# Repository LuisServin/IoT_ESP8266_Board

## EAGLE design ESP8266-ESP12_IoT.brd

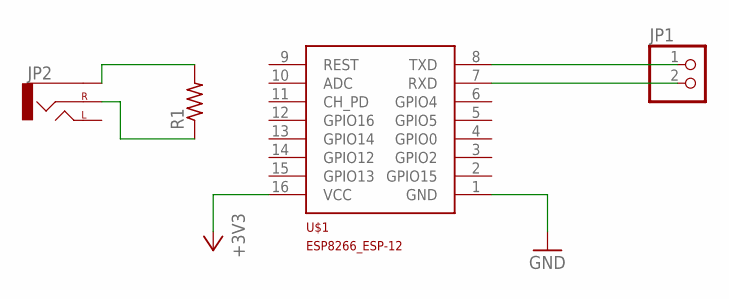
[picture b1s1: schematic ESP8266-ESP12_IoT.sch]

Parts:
JP1: PINHD-1X2/90; 1X02/90
JP2: AUDIO-JACKPTH; AUDIO-JACK
R1: R-US_R0805; R0805
U$1: ESP8266_ESP-12; ESP8266-ESP12

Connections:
+3V3: U$1.16 (VCC)
GND: U$1.1 (GND)
unnamed: JP1.1, U$1.8 (TXD)
unnamed: JP1.2, U$1.7 (RXD)
unnamed: JP2.SLEEVE, R1.2
unnamed: JP2.RING (RIGHT), R1.1

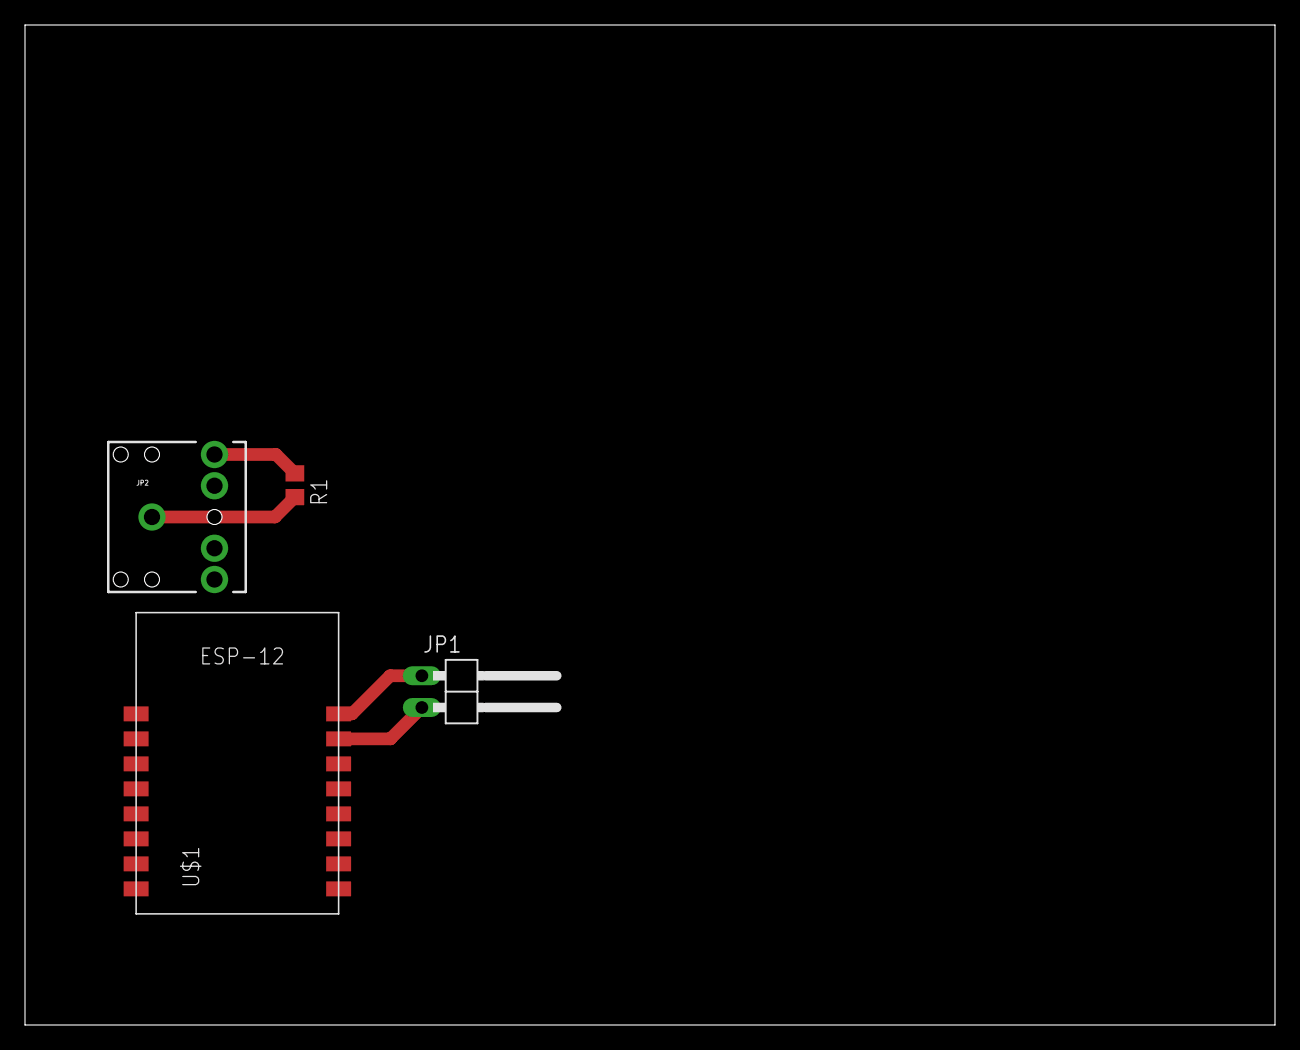
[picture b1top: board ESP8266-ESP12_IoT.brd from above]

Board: 2 copper layers, 100.0 x 80.0 mm, 4 parts (0 on the bottom side), 4 nets.

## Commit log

2015-08-30 Starting
    This is the beginning for the repository of my owm ESP8266 board

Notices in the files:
parts and their libraries:
SparkFun-Connectors: Licensing: Creative Commons ShareAlike 4.0 International - https://creativecommons.org/licenses/by-sa/4.0
